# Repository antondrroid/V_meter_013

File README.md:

# test

hange at remoe and pull to the load.

the somebody edit project

one more time indeendent editing

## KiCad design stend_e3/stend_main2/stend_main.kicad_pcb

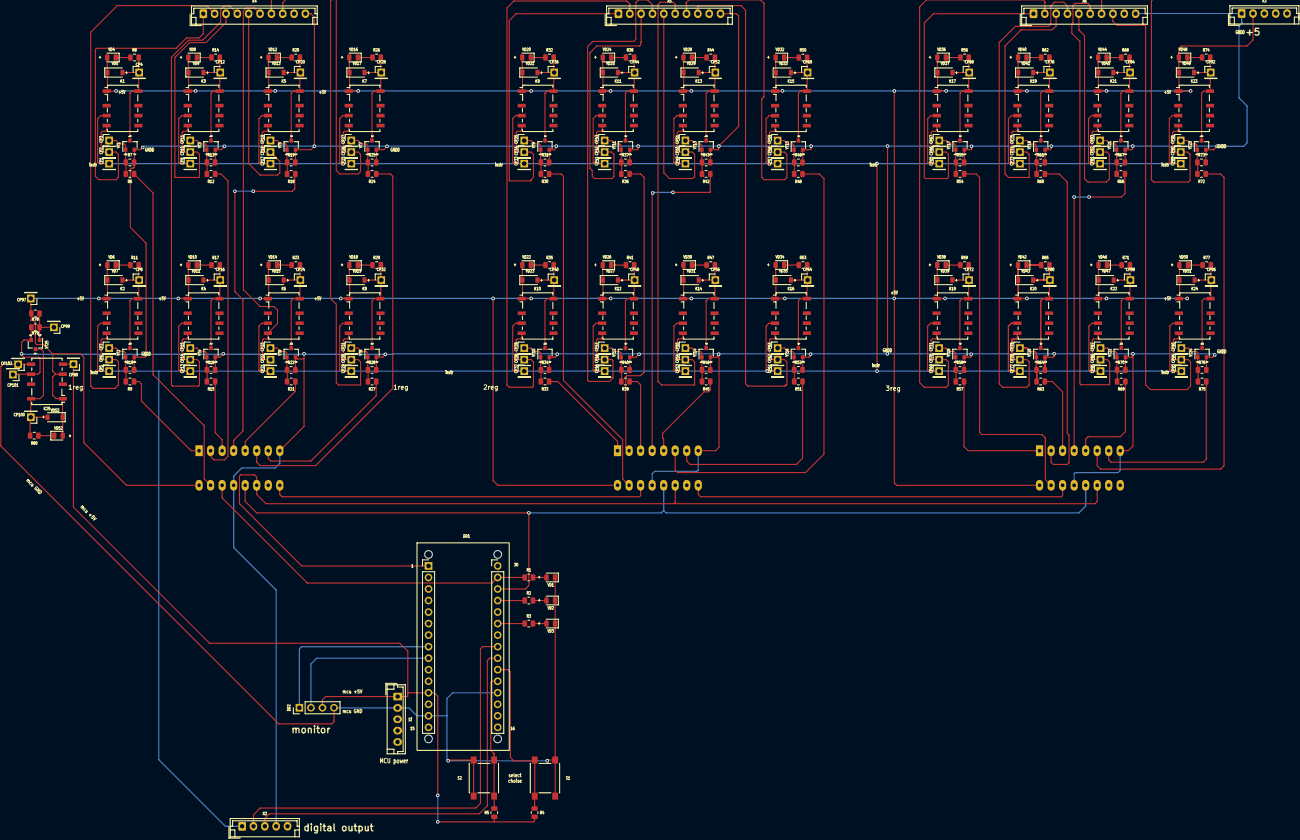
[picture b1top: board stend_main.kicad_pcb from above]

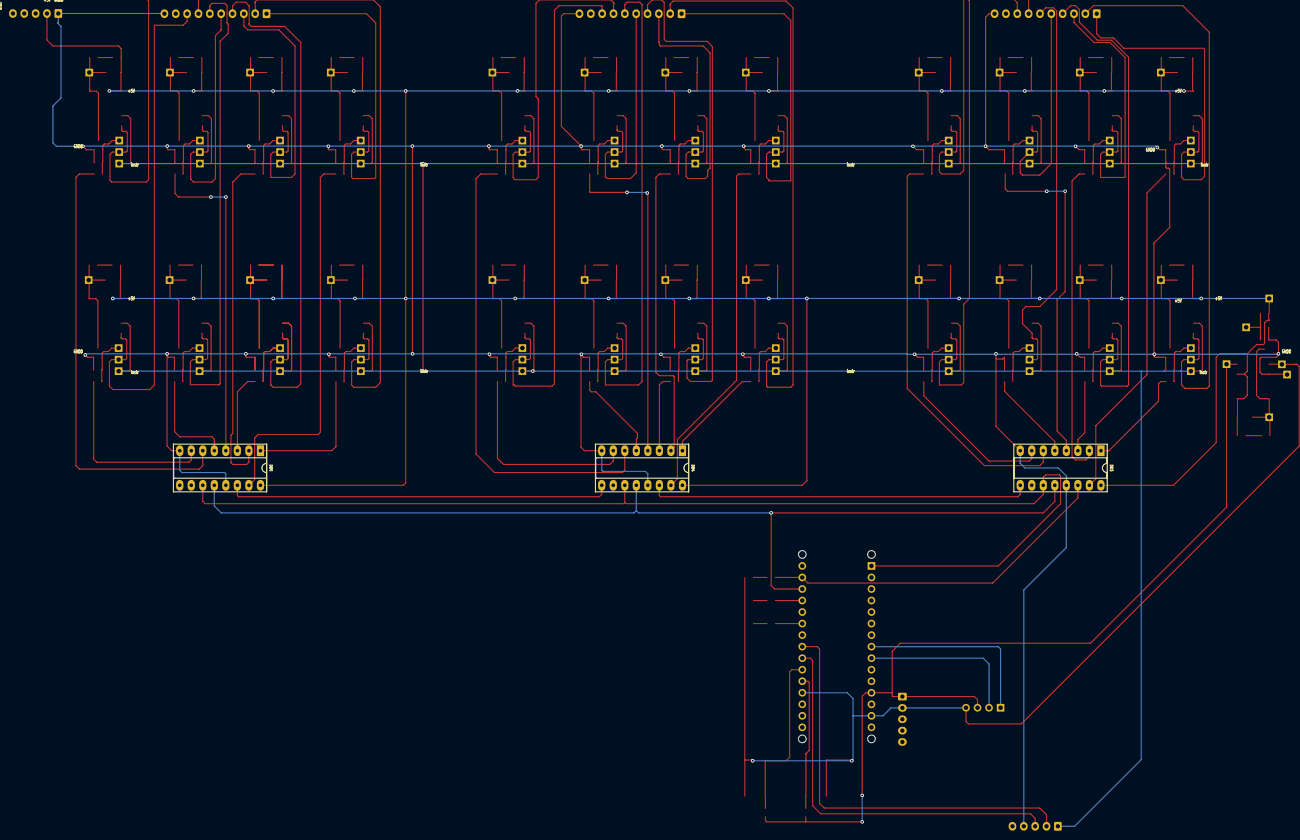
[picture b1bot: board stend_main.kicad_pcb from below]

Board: 2 copper layers, 298 parts (3 on the bottom side), 144 nets.

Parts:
CP1, CP2, CP3, CP5, CP6, CP7, CP9, CP10, CP11, CP13, CP14, CP15, CP17, CP18, CP19, CP21, CP22, CP23, CP25, CP26, CP27, CP29, CP30, CP31, CP33, CP34, CP35, CP37, CP38, CP39, CP41, CP42, CP43, CP45, CP46, CP47, CP49, CP50, CP51, CP53, CP54, CP55, CP57, CP58, CP59, CP61, CP62, CP63, CP65, CP66, CP67, CP69, CP70, CP71, CP73, CP74, CP75, CP77, CP78, CP79, CP81, CP82, CP83, CP85, CP86, CP87, CP89, CP90, CP91, CP93, CP94, CP95, CP97, CP98, CP99: CP_L; PinHeader_1x01_P2.54mm_Vertical
CP4, CP8, CP12, CP16, CP20, CP24, CP28, CP32, CP36, CP40, CP44, CP48, CP52, CP56, CP60, CP64, CP68, CP72, CP76, CP80, CP84, CP88, CP92, CP96, CP100, CP101, CP102: CP_R; PinHeader_1x01_P2.54mm_Vertical
DD1: NANO_ATmega328; Nano_328pu
DD2: Display_1306; PinHeader_1x04_P2.54mm_Vertical
DD3, DD4, DD5: 74HC595; DIP-16_W7.62mm_Socket_LongPads
K1, K2, K3, K4, K5, K6, K7, K8, K9, K10, K11, K12, K13, K14, K15, K16, K17, K18, K19, K20, K21, K22, K23, K24, K25: G6K-2F-Y-5VDC_L; Relay_DPDT_Omron_G6K-2F-Y
R1, R2, R3, R4, R5: 33k; R_0805_2012Metric
R6, R9, R12, R15, R18, R21, R24, R27, R30, R33, R36, R39, R42, R45, R48, R51, R54, R57, R60, R63, R66, R69, R72, R75, R78: 2.2k; R_0805_2012Metric
R7, R10, R13, R16, R19, R22, R25, R28, R31, R34, R37, R40, R43, R46, R49, R52, R55, R58, R61, R64, R67, R70, R73, R76, R79: 2.2kvert; R_0805_2012Metric
R8, R11, R14, R17, R20, R23, R26, R29, R32, R35, R38, R41, R44, R47, R50, R53, R56, R59, R62, R65, R68, R71, R74, R77, R80: 12k; R_0805_2012Metric
S1, S2: taktile button KLS7; SW_Push_2P1T_6x6mm
VD1, VD2, VD3, VD4, VD6, VD8, VD10, VD12, VD14, VD16, VD18, VD20, VD22, VD24, VD26, VD28, VD30, VD32, VD34, VD36, VD38, VD40, VD42, VD44, VD46, VD48, VD50, VD52: LED; LED_0805_2012Metric
VD5, VD7, VD9, VD11, VD13, VD15, VD17, VD19, VD21, VD23, VD25, VD27, VD29, VD31, VD33, VD35, VD37, VD39, VD41, VD43, VD45, VD47, VD49, VD51, VD53: 1N4148W; D_SOD-123
VT1, VT2, VT3, VT4, VT5, VT6, VT7, VT8, VT9, VT10, VT11, VT12, VT13, VT14, VT15, VT16, VT17, VT18, VT19, VT20, VT21, VT22, VT23, VT24, VT25: 2SC1815; SOT-23_MY_C_E_Silk
X1: JST-B2B-XHA_Left; JST_EH_B5B-EH-A_1x05_P2.50mm_Vertical
X2, X3: B5B-XH-A_Left; JST_EH_B5B-EH-A_1x05_P2.50mm_Vertical
X4, X5, X6: B10B-XH-A_right; JST_EH_B10B-EH-A_1x10_P2.50mm_Vertical

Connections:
+5V: CP97.1, DD3.16 (VCC), DD4.16 (VCC), DD5.16 (VCC), K1.1, K2.1, K3.1, K4.1, K5.1, K6.1, K7.1, K8.1, K9.1, K10.1, K11.1, K12.1, K13.1, K14.1, K15.1, K16.1, K17.1, K18.1, K19.1, K20.1, K21.1, K22.1, K23.1, K24.1, K25.1, K25.3, R78.1, VD4.2 (A), VD5.1 (K), VD6.2 (A), VD7.1 (K), VD8.2 (A), VD9.1 (K), VD10.2 (A), VD11.1 (K), VD12.2 (A), VD13.1 (K), VD14.2 (A), VD15.1 (K), VD16.2 (A), VD17.1 (K), VD18.2 (A), VD19.1 (K), VD20.2 (A), VD21.1 (K), VD22.2 (A), VD23.1 (K), VD24.2 (A), VD25.1 (K), VD26.2 (A), VD27.1 (K), VD28.2 (A), VD29.1 (K), VD30.2 (A), VD31.1 (K), VD32.2 (A), VD33.1 (K), VD34.2 (A), VD35.1 (K), VD36.2 (A), VD37.1 (K), VD38.2 (A), VD39.1 (K), VD40.2 (A), VD41.1 (K), VD42.2 (A), VD43.1 (K), VD44.2 (A), VD45.1 (K), VD46.2 (A), VD47.1 (K), VD48.2 (A), VD49.1 (K), VD50.2 (A), VD51.1 (K), VD52.2 (A), VD53.1 (K), X3.2
/2_MCU/CS/SS: DD1.28 (D10/PB2(CS/SS)), DD3.12 (RCLK), DD4.12 (RCLK), DD5.12 (RCLK)
/2_MCU/MOSI: DD1.29 (D11/PB3(MOSI)), DD3.14 (SER), R1.1
/2_MCU/SCK: DD1.1 (D13/PB5(SCK)), DD3.11 (SRCLK), DD4.11 (SRCLK), DD5.11 (SRCLK)
/2_MCU/SYNC IN: DD1.22 (D4/PD4), X2.3
/2_MCU/SYNC OUT: DD1.23 (D5/PD5), X2.2
/CTRL1: CP2.1, K1.4, X4.1
/CTRL2: CP6.1, K2.4, X4.2
/CTRL3: CP10.1, K3.4, X4.3
/CTRL4: CP14.1, K4.4, X4.4
/CTRL5: CP18.1, K5.4, X4.5
/CTRL6: CP22.1, K6.4, X4.6
/CTRL7: CP26.1, K7.4, X4.7
/CTRL8: CP30.1, K8.4, X4.8
/CTRL9: CP34.1, K9.4, X5.1
/CTRL10: CP38.1, K10.4, X5.2
/CTRL11: CP42.1, K11.4, X5.3
/CTRL12: CP46.1, K12.4, X5.4
/CTRL13: CP50.1, K13.4, X5.5
/CTRL14: CP54.1, K14.4, X5.6
/CTRL15: CP58.1, K15.4, X5.7
/CTRL16: CP62.1, K16.4, X5.8
/CTRL17: CP66.1, K17.4, X6.1
/CTRL18: CP70.1, K18.4, X6.2
/CTRL19: CP74.1, K19.4, X6.3
/CTRL20: CP78.1, K20.4, X6.4
/CTRL21: CP82.1, K21.4, X6.5
/CTRL22: CP86.1, K22.4, X6.6
/CTRL23: CP90.1, K23.4, X6.7
/CTRL24: CP94.1, K24.4, X6.8
/INSTR+: CP1.1, CP5.1, CP9.1, CP13.1, CP17.1, CP21.1, CP25.1, CP29.1, CP33.1, CP37.1, CP41.1, CP45.1, CP49.1, CP53.1, CP57.1, CP61.1, CP65.1, CP69.1, CP73.1, CP77.1, CP81.1, CP85.1, CP89.1, CP93.1, K1.3, K2.3, K3.3, K4.3, K5.3, K6.3, K7.3, K8.3, K9.3, K10.3, K11.3, K12.3, K13.3, K14.3, K15.3, K16.3, K17.3, K18.3, K19.3, K20.3, K21.3, K22.3, K23.3, K24.3, X2.1
/MCU+: CP98.1, DD1.12 (+5V), DD2.3 (VCC), K25.4, R4.2, R5.1, X1.1
/MCU_GND: CP102.1, DD1.14 (GND), DD1.19 (GND), DD2.4 (GND), K25.5, S1.2, S2.2, VD1.1 (K), VD2.1 (K), VD3.1 (K), X1.2
/RL1: DD3.15 (QA), R6.1
/RL2: DD3.1 (QB), R9.1
/RL3: DD3.2 (QC), R12.1
/RL4: DD3.3 (QD), R15.1
/RL5: DD3.4 (QE), R18.1
/RL6: DD3.5 (QF), R21.1
/RL7: DD3.6 (QG), R24.1
/RL8: DD3.7 (QH), R27.1
/RL9: DD4.15 (QA), R30.1
/RL10: DD4.1 (QB), R33.1
/RL11: DD4.2 (QC), R36.1
/RL12: DD4.3 (QD), R39.1
/RL13: DD4.4 (QE), R42.1
/RL14: DD4.5 (QF), R45.1
/RL15: DD4.6 (QG), R48.1
/RL16: DD4.7 (QH), R51.1
/RL17: DD5.15 (QA), R54.1
/RL18: DD5.1 (QB), R57.1
/RL19: DD5.2 (QC), R60.1
/RL20: DD5.3 (QD), R63.1
/RL21: DD5.4 (QE), R66.1
/RL22: DD5.5 (QF), R69.1
/RL23: DD5.6 (QG), R72.1
/RL24: DD5.7 (QH), R75.1
GNDD: CP101.1, DD3.8 (GND), DD3.13 (~OE), DD4.8 (GND), DD4.13 (~OE), DD5.8 (GND), DD5.13 (~OE), K25.6, R7.2, R10.2, R13.2, R16.2, R19.2, R22.2, R25.2, R28.2, R31.2, R34.2, R37.2, R40.2, R43.2, R46.2, R49.2, R52.2, R55.2, R58.2, R61.2, R64.2, R67.2, R70.2, R73.2, R76.2, R79.2, VT1.2 (E), VT2.2 (E), VT3.2 (E), VT4.2 (E), VT5.2 (E), VT6.2 (E), VT7.2 (E), VT8.2 (E), VT9.2 (E), VT10.2 (E), VT11.2 (E), VT12.2 (E), VT13.2 (E), VT14.2 (E), VT15.2 (E), VT16.2 (E), VT17.2 (E), VT18.2 (E), VT19.2 (E), VT20.2 (E), VT21.2 (E), VT22.2 (E), VT23.2 (E), VT24.2 (E), VT25.2 (E), X2.4, X2.5, X3.1, X4.10, X5.10, X6.10
unnamed: CP3.1, R6.2, R7.1, VT1.1 (B)
unnamed: CP4.1, K1.8, R8.2, VD5.2 (A), VT1.3 (C)
unnamed: CP7.1, R9.2, R10.1, VT2.1 (B)
unnamed: CP8.1, K2.8, R11.2, VD7.2 (A), VT2.3 (C)
unnamed: CP11.1, R12.2, R13.1, VT3.1 (B)
unnamed: CP12.1, K3.8, R14.2, VD9.2 (A), VT3.3 (C)
unnamed: CP15.1, R15.2, R16.1, VT4.1 (B)
unnamed: CP16.1, K4.8, R17.2, VD11.2 (A), VT4.3 (C)
unnamed: CP19.1, R18.2, R19.1, VT5.1 (B)
unnamed: CP20.1, K5.8, R20.2, VD13.2 (A), VT5.3 (C)
unnamed: CP23.1, R21.2, R22.1, VT6.1 (B)
unnamed: CP24.1, K6.8, R23.2, VD15.2 (A), VT6.3 (C)
unnamed: CP27.1, R24.2, R25.1, VT7.1 (B)
unnamed: CP28.1, K7.8, R26.2, VD17.2 (A), VT7.3 (C)
unnamed: CP31.1, R27.2, R28.1, VT8.1 (B)
unnamed: CP32.1, K8.8, R29.2, VD19.2 (A), VT8.3 (C)
unnamed: CP35.1, R30.2, R31.1, VT9.1 (B)
unnamed: CP36.1, K9.8, R32.2, VD21.2 (A), VT9.3 (C)
unnamed: CP39.1, R33.2, R34.1, VT10.1 (B)
unnamed: CP40.1, K10.8, R35.2, VD23.2 (A), VT10.3 (C)
unnamed: CP43.1, R36.2, R37.1, VT11.1 (B)
unnamed: CP44.1, K11.8, R38.2, VD25.2 (A), VT11.3 (C)
unnamed: CP47.1, R39.2, R40.1, VT12.1 (B)
unnamed: CP48.1, K12.8, R41.2, VD27.2 (A), VT12.3 (C)
unnamed: CP51.1, R42.2, R43.1, VT13.1 (B)
unnamed: CP52.1, K13.8, R44.2, VD29.2 (A), VT13.3 (C)
unnamed: CP55.1, R45.2, R46.1, VT14.1 (B)
unnamed: CP56.1, K14.8, R47.2, VD31.2 (A), VT14.3 (C)
unnamed: CP59.1, R48.2, R49.1, VT15.1 (B)
unnamed: CP60.1, K15.8, R50.2, VD33.2 (A), VT15.3 (C)
unnamed: CP63.1, R51.2, R52.1, VT16.1 (B)
unnamed: CP64.1, K16.8, R53.2, VD35.2 (A), VT16.3 (C)
unnamed: CP67.1, R54.2, R55.1, VT17.1 (B)
unnamed: CP68.1, K17.8, R56.2, VD37.2 (A), VT17.3 (C)
unnamed: CP71.1, R57.2, R58.1, VT18.1 (B)
unnamed: CP72.1, K18.8, R59.2, VD39.2 (A), VT18.3 (C)
unnamed: CP75.1, R60.2, R61.1, VT19.1 (B)
unnamed: CP76.1, K19.8, R62.2, VD41.2 (A), VT19.3 (C)
unnamed: CP79.1, R63.2, R64.1, VT20.1 (B)
unnamed: CP80.1, K20.8, R65.2, VD43.2 (A), VT20.3 (C)
unnamed: CP83.1, R66.2, R67.1, VT21.1 (B)
unnamed: CP84.1, K21.8, R68.2, VD45.2 (A), VT21.3 (C)
unnamed: CP87.1, R69.2, R70.1, VT22.1 (B)
unnamed: CP88.1, K22.8, R71.2, VD47.2 (A), VT22.3 (C)
unnamed: CP91.1, R72.2, R73.1, VT23.1 (B)
unnamed: CP92.1, K23.8, R74.2, VD49.2 (A), VT23.3 (C)
unnamed: CP95.1, R75.2, R76.1, VT24.1 (B)
unnamed: CP96.1, K24.8, R77.2, VD51.2 (A), VT24.3 (C)
unnamed: CP99.1, R78.2, R79.1, VT25.1 (B)
unnamed: CP100.1, K25.8, R80.2, VD53.2 (A), VT25.3 (C)
unnamed: DD1.8 (A4/PC4), DD2.1 (SDA)
unnamed: DD1.9 (A5/PC5), DD2.2 (SCL)
unnamed: DD1.20 (D2/PD2), R5.2, S2.1
unnamed: DD1.21 (D3/PD3), R4.1, S1.1
unnamed: DD1.25 (D7/PD7), R3.1
unnamed: DD1.27 (D9/PB1), R2.1
unnamed: DD3.9 (QH'), DD4.14 (SER)
unnamed: DD4.9 (QH'), DD5.14 (SER)
unnamed: R1.2, VD1.2 (A)
unnamed: R2.2, VD2.2 (A)
unnamed: R3.2, VD3.2 (A)
unnamed: R8.1, VD4.1 (K)
unnamed: R11.1, VD6.1 (K)
unnamed: R14.1, VD8.1 (K)
unnamed: R17.1, VD10.1 (K)
unnamed: R20.1, VD12.1 (K)
unnamed: R23.1, VD14.1 (K)
unnamed: R26.1, VD16.1 (K)
unnamed: R29.1, VD18.1 (K)
unnamed: R32.1, VD20.1 (K)
unnamed: R35.1, VD22.1 (K)
unnamed: R38.1, VD24.1 (K)
unnamed: R41.1, VD26.1 (K)
unnamed: R44.1, VD28.1 (K)
unnamed: R47.1, VD30.1 (K)
unnamed: R50.1, VD32.1 (K)
unnamed: R53.1, VD34.1 (K)
unnamed: R56.1, VD36.1 (K)
unnamed: R59.1, VD38.1 (K)
unnamed: R62.1, VD40.1 (K)
unnamed: R65.1, VD42.1 (K)
unnamed: R68.1, VD44.1 (K)
unnamed: R71.1, VD46.1 (K)
unnamed: R74.1, VD48.1 (K)
unnamed: R77.1, VD50.1 (K)
unnamed: R80.1, VD52.1 (K)

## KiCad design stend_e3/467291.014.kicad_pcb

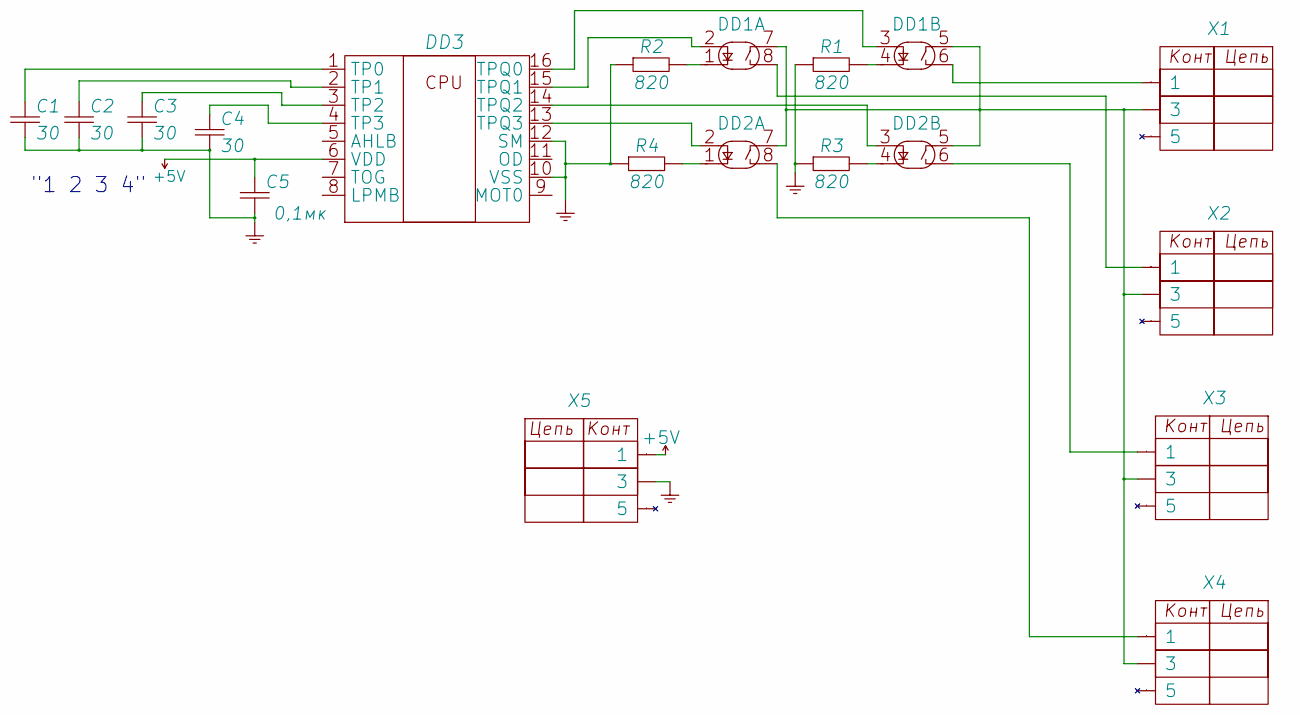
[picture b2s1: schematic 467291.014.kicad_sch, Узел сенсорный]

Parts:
C1, C2, C3, C4: K10-69v-MP0-50V-2012M-30pF-10%-[LTM][Capacitors][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; [LTM][C][0805][2012M]
C5: K10-69v-N90-25V-2012M-0,1uF+80-20%-[LTM][Capacito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; [LTM][C][0805][2012M]
DD1, DD2: kR293KP3AT-Isolator; DIP-8_W8.89mm_SMDSocket_LongPads
DD3: kikadtest1-cache_TP224_Sensor-kikadtest1-cache; HTSSOP-16-1EP_4x5mm
R1, R2, R3, R4: R1-12-0,125-820Ohm-5%-M-[LTM][Resistors][R112][08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; [LTM][R][0805][2012M]
X1, X2, X3, X4: snp346-5RP21-1_3cont-[LTM][Connectors][СНП346][5]; button_sensor_18mm
X5: snp346-5RP21-1_3cont-[LTM][Connectors][СНП346][5]; button_1x3_P5mm_Vert_longHoles

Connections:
+5V: C5.2, DD3.6 (VDD), X5.1
unnamed: C1.2, DD3.1 (TP0)
unnamed: C2.2, DD3.2 (TP1)
unnamed: C3.2, DD3.3 (TP2)
unnamed: C4.2, DD3.4 (TP3)
unnamed: DD1.1, R2.2
unnamed: DD1.2, DD3.15 (TPQ1)
unnamed: DD1.3, DD3.16 (TPQ0)
unnamed: DD1.4, R1.2
unnamed: DD1.5, DD1.7, DD2.5, DD2.7, X1.3, X2.3, X3.3, X4.3
unnamed: DD1.6, X1.1
unnamed: DD1.8, X2.1
unnamed: DD2.1, R4.2
unnamed: DD2.2, DD3.13 (TPQ3)
unnamed: DD2.3, DD3.14 (TPQ2)
unnamed: DD2.4, R3.2
unnamed: DD2.6, X3.1
unnamed: DD2.8, X4.1

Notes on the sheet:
"1 2 3 4"

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
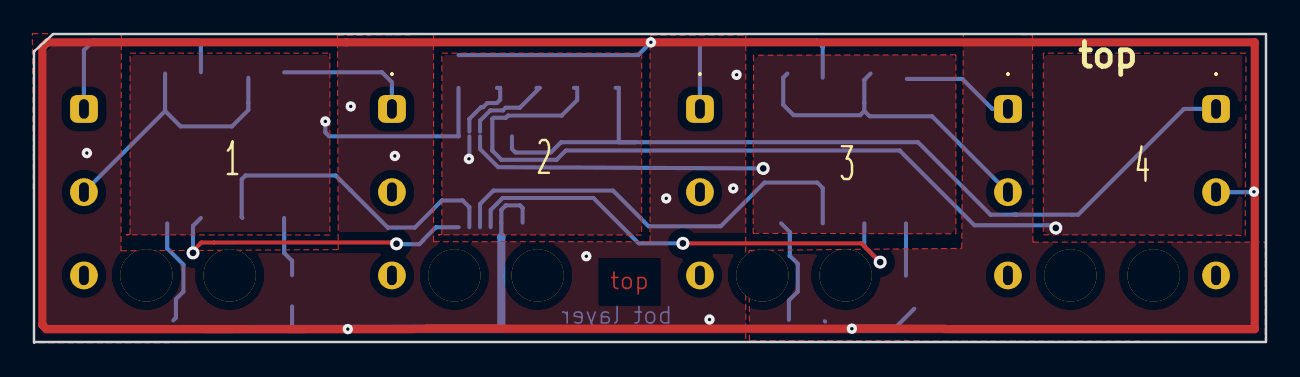
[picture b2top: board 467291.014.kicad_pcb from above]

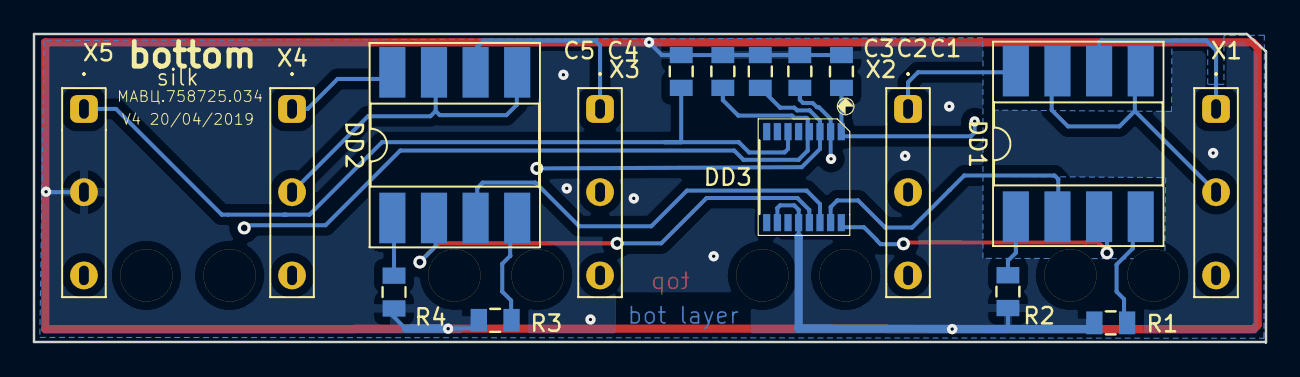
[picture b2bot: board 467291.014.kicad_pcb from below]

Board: 32 copper layers, 75.2 x 18.8 mm, 17 parts (17 on the bottom side), 19 nets.

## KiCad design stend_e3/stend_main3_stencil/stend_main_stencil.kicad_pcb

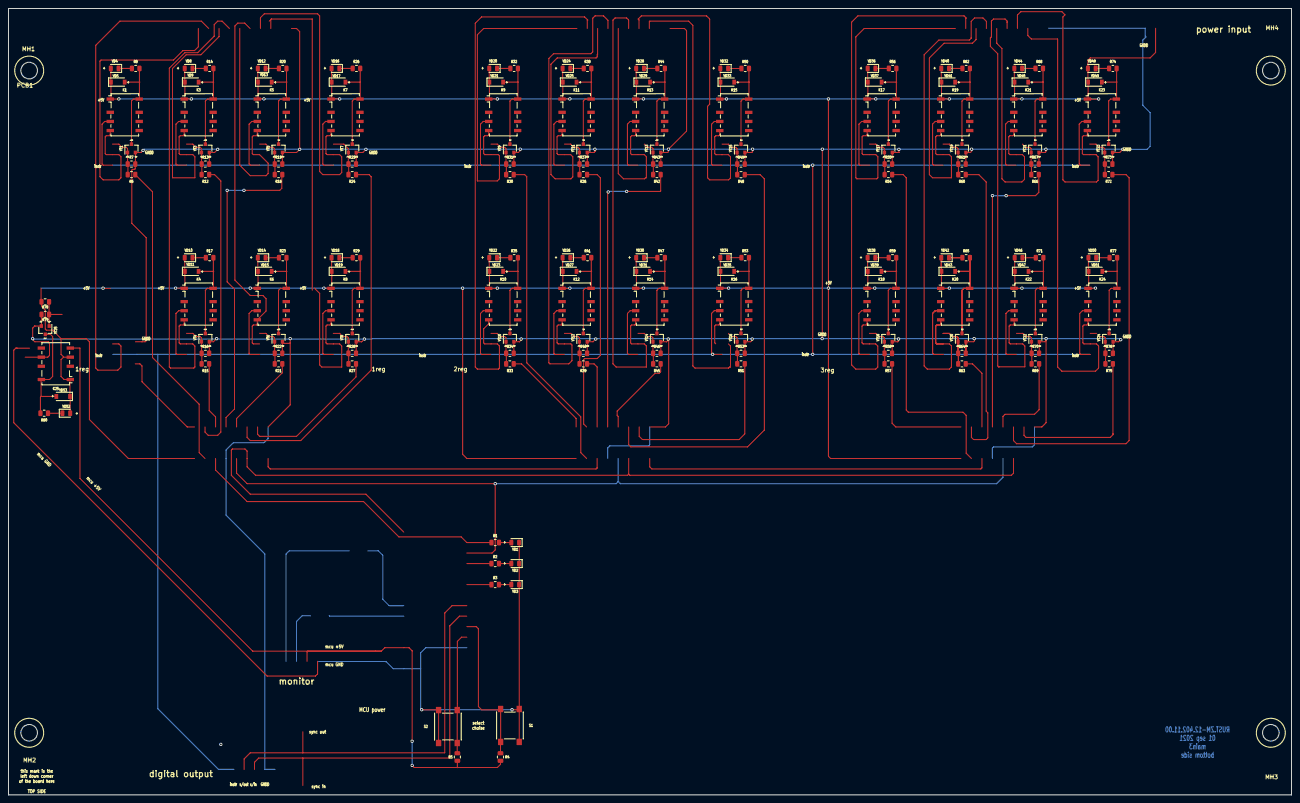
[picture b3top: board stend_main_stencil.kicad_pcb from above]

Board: 2 copper layers, 310.0 x 190.0 mm, 179 parts (0 on the bottom side), 82 nets.

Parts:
K1, K3, K4, K5, K6, K7, K8, K9, K10, K11, K12, K13, K14, K15, K16, K17, K18, K19, K20, K21, K22, K23, K24, K25: G6K-2F-Y-5VDC_L; Relay_DPDT_Omron_G6K-2F-Y
PCB1: board_symbol_190x310; board_fp_190x310
R1, R2, R3, R4, R5: 33k; R_0805_2012Metric
R6, R12, R15, R18, R21, R24, R27, R30, R33, R36, R39, R42, R45, R48, R51, R54, R57, R60, R63, R66, R69, R72, R75, R78: 2.2k; R_0805_2012Metric
R7, R13, R16, R19, R22, R25, R28, R31, R34, R37, R40, R43, R46, R49, R52, R55, R58, R61, R64, R67, R70, R73, R76, R79: 2.2kvert; R_0805_2012Metric
R8, R14, R17, R20, R23, R26, R29, R32, R35, R38, R41, R44, R47, R50, R53, R56, R59, R62, R65, R68, R71, R74, R77, R80: 12k; R_0805_2012Metric
S1, S2: taktile button KLS7; SW_Push_2P1T_6x6mm
VD1, VD2, VD3, VD4, VD8, VD10, VD12, VD14, VD16, VD18, VD20, VD22, VD24, VD26, VD28, VD30, VD32, VD34, VD36, VD38, VD40, VD42, VD44, VD46, VD48, VD50, VD52: LED; LED_0805_2012Metric
VD5, VD9, VD11, VD13, VD15, VD17, VD19, VD21, VD23, VD25, VD27, VD29, VD31, VD33, VD35, VD37, VD39, VD41, VD43, VD45, VD47, VD49, VD51, VD53: 1N4148W; D_SOD-123
VT1, VT3, VT4, VT5, VT6, VT7, VT8, VT9, VT10, VT11, VT12, VT13, VT14, VT15, VT16, VT17, VT18, VT19, VT20, VT21, VT22, VT23, VT24, VT25: 2SC1815; SOT-23_MY_C_E_Silk

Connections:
+5V: K1.1, K3.1, K4.1, K5.1, K6.1, K7.1, K8.1, K9.1, K10.1, K11.1, K12.1, K13.1, K14.1, K15.1, K16.1, K17.1, K18.1, K19.1, K20.1, K21.1, K22.1, K23.1, K24.1, K25.1, K25.3, R78.1, VD4.2 (A), VD5.1 (K), VD8.2 (A), VD9.1 (K), VD10.2 (A), VD11.1 (K), VD12.2 (A), VD13.1 (K), VD14.2 (A), VD15.1 (K), VD16.2 (A), VD17.1 (K), VD18.2 (A), VD19.1 (K), VD20.2 (A), VD21.1 (K), VD22.2 (A), VD23.1 (K), VD24.2 (A), VD25.1 (K), VD26.2 (A), VD27.1 (K), VD28.2 (A), VD29.1 (K), VD30.2 (A), VD31.1 (K), VD32.2 (A), VD33.1 (K), VD34.2 (A), VD35.1 (K), VD36.2 (A), VD37.1 (K), VD38.2 (A), VD39.1 (K), VD40.2 (A), VD41.1 (K), VD42.2 (A), VD43.1 (K), VD44.2 (A), VD45.1 (K), VD46.2 (A), VD47.1 (K), VD48.2 (A), VD49.1 (K), VD50.2 (A), VD51.1 (K), VD52.2 (A), VD53.1 (K)
/INSTR+: K1.3, K3.3, K4.3, K5.3, K6.3, K7.3, K8.3, K9.3, K10.3, K11.3, K12.3, K13.3, K14.3, K15.3, K16.3, K17.3, K18.3, K19.3, K20.3, K21.3, K22.3, K23.3, K24.3
/MCU+: K25.4, R4.2, R5.1
/MCU_GND: K25.5, S1.2, S2.2, VD1.1 (K), VD2.1 (K), VD3.1 (K)
GNDD: K25.6, R7.2, R13.2, R16.2, R19.2, R22.2, R25.2, R28.2, R31.2, R34.2, R37.2, R40.2, R43.2, R46.2, R49.2, R52.2, R55.2, R58.2, R61.2, R64.2, R67.2, R70.2, R73.2, R76.2, R79.2, VT1.2 (E), VT3.2 (E), VT4.2 (E), VT5.2 (E), VT6.2 (E), VT7.2 (E), VT8.2 (E), VT9.2 (E), VT10.2 (E), VT11.2 (E), VT12.2 (E), VT13.2 (E), VT14.2 (E), VT15.2 (E), VT16.2 (E), VT17.2 (E), VT18.2 (E), VT19.2 (E), VT20.2 (E), VT21.2 (E), VT22.2 (E), VT23.2 (E), VT24.2 (E), VT25.2 (E)
unnamed: R6.2, R7.1, VT1.1 (B)
unnamed: K1.8, R8.2, VD5.2 (A), VT1.3 (C)
unnamed: R12.2, R13.1, VT3.1 (B)
unnamed: K3.8, R14.2, VD9.2 (A), VT3.3 (C)
unnamed: R15.2, R16.1, VT4.1 (B)
unnamed: K4.8, R17.2, VD11.2 (A), VT4.3 (C)
unnamed: R18.2, R19.1, VT5.1 (B)
unnamed: K5.8, R20.2, VD13.2 (A), VT5.3 (C)
unnamed: R21.2, R22.1, VT6.1 (B)
unnamed: K6.8, R23.2, VD15.2 (A), VT6.3 (C)
unnamed: R24.2, R25.1, VT7.1 (B)
unnamed: K7.8, R26.2, VD17.2 (A), VT7.3 (C)
unnamed: R27.2, R28.1, VT8.1 (B)
unnamed: K8.8, R29.2, VD19.2 (A), VT8.3 (C)
unnamed: R30.2, R31.1, VT9.1 (B)
unnamed: K9.8, R32.2, VD21.2 (A), VT9.3 (C)
unnamed: R33.2, R34.1, VT10.1 (B)
unnamed: K10.8, R35.2, VD23.2 (A), VT10.3 (C)
unnamed: R36.2, R37.1, VT11.1 (B)
unnamed: K11.8, R38.2, VD25.2 (A), VT11.3 (C)
unnamed: R39.2, R40.1, VT12.1 (B)
unnamed: K12.8, R41.2, VD27.2 (A), VT12.3 (C)
unnamed: R42.2, R43.1, VT13.1 (B)
unnamed: K13.8, R44.2, VD29.2 (A), VT13.3 (C)
unnamed: R45.2, R46.1, VT14.1 (B)
unnamed: K14.8, R47.2, VD31.2 (A), VT14.3 (C)
unnamed: R48.2, R49.1, VT15.1 (B)
unnamed: K15.8, R50.2, VD33.2 (A), VT15.3 (C)
unnamed: R51.2, R52.1, VT16.1 (B)
unnamed: K16.8, R53.2, VD35.2 (A), VT16.3 (C)
unnamed: R54.2, R55.1, VT17.1 (B)
unnamed: K17.8, R56.2, VD37.2 (A), VT17.3 (C)
unnamed: R57.2, R58.1, VT18.1 (B)
unnamed: K18.8, R59.2, VD39.2 (A), VT18.3 (C)
unnamed: R60.2, R61.1, VT19.1 (B)
unnamed: K19.8, R62.2, VD41.2 (A), VT19.3 (C)
unnamed: R63.2, R64.1, VT20.1 (B)
unnamed: K20.8, R65.2, VD43.2 (A), VT20.3 (C)
unnamed: R66.2, R67.1, VT21.1 (B)
unnamed: K21.8, R68.2, VD45.2 (A), VT21.3 (C)
unnamed: R69.2, R70.1, VT22.1 (B)
unnamed: K22.8, R71.2, VD47.2 (A), VT22.3 (C)
unnamed: R72.2, R73.1, VT23.1 (B)
unnamed: K23.8, R74.2, VD49.2 (A), VT23.3 (C)
unnamed: R75.2, R76.1, VT24.1 (B)
unnamed: K24.8, R77.2, VD51.2 (A), VT24.3 (C)
unnamed: R78.2, R79.1, VT25.1 (B)
unnamed: K25.8, R80.2, VD53.2 (A), VT25.3 (C)
unnamed: R5.2, S2.1
unnamed: R4.1, S1.1
unnamed: R1.2, VD1.2 (A)
unnamed: R2.2, VD2.2 (A)
unnamed: R3.2, VD3.2 (A)
unnamed: R8.1, VD4.1 (K)
unnamed: R14.1, VD8.1 (K)
unnamed: R17.1, VD10.1 (K)
unnamed: R20.1, VD12.1 (K)
unnamed: R23.1, VD14.1 (K)
unnamed: R26.1, VD16.1 (K)
unnamed: R29.1, VD18.1 (K)
unnamed: R32.1, VD20.1 (K)
unnamed: R35.1, VD22.1 (K)
unnamed: R38.1, VD24.1 (K)
unnamed: R41.1, VD26.1 (K)
unnamed: R44.1, VD28.1 (K)
unnamed: R47.1, VD30.1 (K)
unnamed: R50.1, VD32.1 (K)
unnamed: R53.1, VD34.1 (K)
unnamed: R56.1, VD36.1 (K)
unnamed: R59.1, VD38.1 (K)
unnamed: R62.1, VD40.1 (K)
unnamed: R65.1, VD42.1 (K)
unnamed: R68.1, VD44.1 (K)
unnamed: R71.1, VD46.1 (K)
unnamed: R74.1, VD48.1 (K)
unnamed: R77.1, VD50.1 (K)
unnamed: R80.1, VD52.1 (K)

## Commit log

2024-08-06 first comit in 2024
2024-08-07 add readme with git manual
